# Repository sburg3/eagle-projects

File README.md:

# eagle-projects
Various projects using CadSoft Eagle.

Including:
* Seven-segment clock with atmega328 microcontroller.
* Analog ammeter clock
* Audio jack to ADC adapter for Digilent Nexys 4 DDR FPGA.

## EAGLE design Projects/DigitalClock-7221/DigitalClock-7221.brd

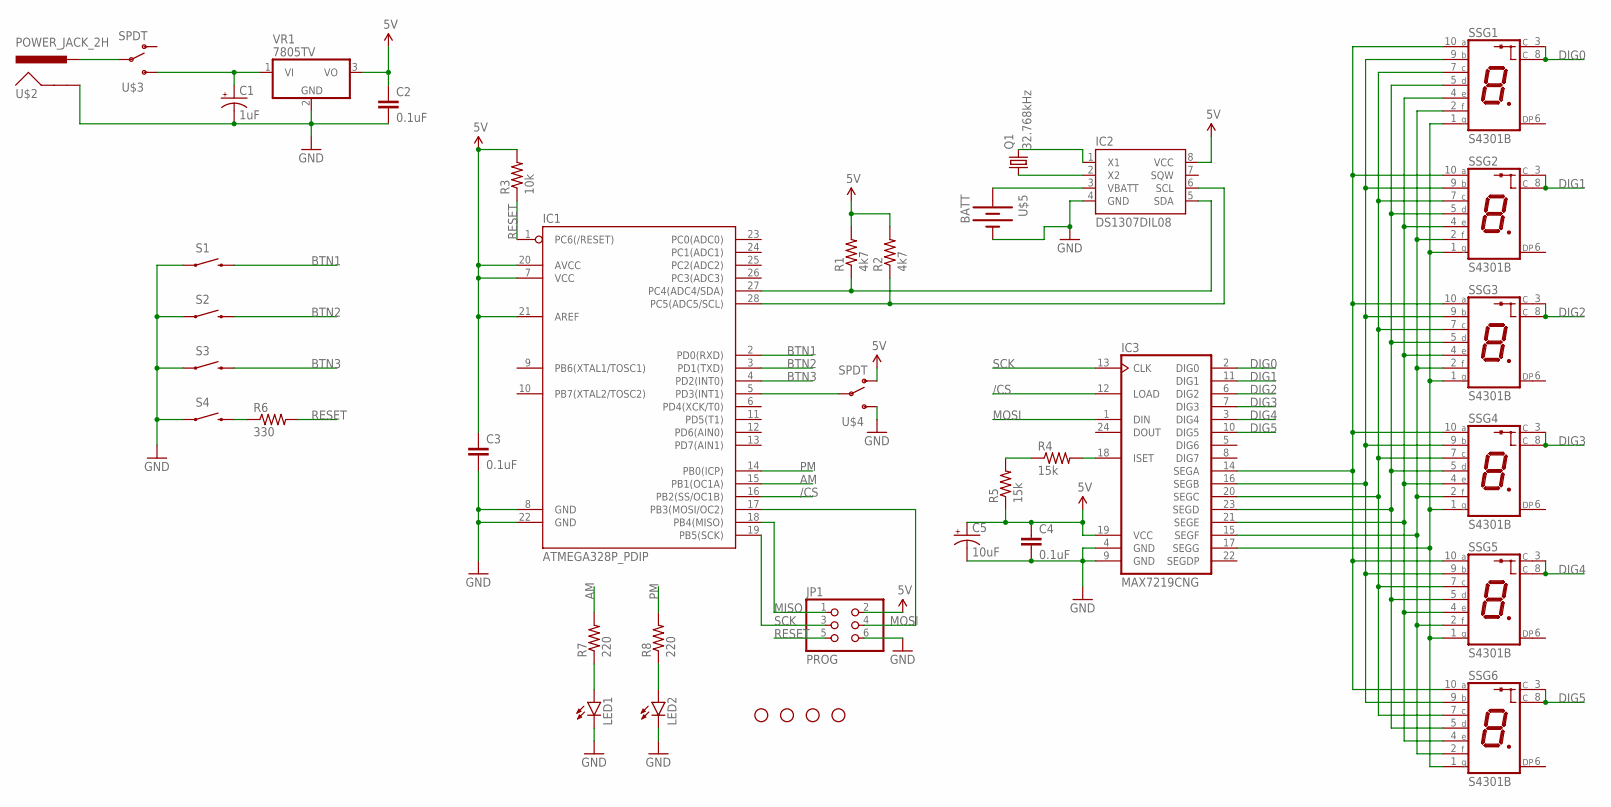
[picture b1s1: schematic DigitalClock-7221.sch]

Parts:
C1: 1uF; CPOL-RADIAL-10UF-25V
C2, C3, C4: 0.1uF; CAP-PTH-5MM
C5: 10uF; CPOL-RADIAL-10UF-25V
H1, H2, H3, H4: STAND-OFF
IC1: ATMEGA328P_PDIP; DIL28-3
IC2: DS1307DIL08; DIL08
IC3: MAX7219CNG; DIL24-3
JP1: PROG; 2X03
LED1, LED2: LED5MM
Q1: 32.768kHz; TC26V
R1, R2: 4k7; AXIAL-0.3
R3: 10k; AXIAL-0.3
R4, R5: 15k; AXIAL-0.3
R6: 330; AXIAL-0.3
R7, R8: 220; AXIAL-0.3
S1, S2, S3, S4: SWITCH-MOMENTARY-2PTH; TACTILE-PTH
SSG1, SSG2, SSG3, SSG4, SSG5, SSG6: S4301B
U$2: POWER_JACK_2H
U$3, U$4: SPDT
U$5: BATT
VR1: 7805TV; TO220V

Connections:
5V: C2.1, C3.1, C4.1, C5.1 (+), IC1.7 (VCC), IC1.20 (AVCC), IC1.21 (AREF), IC2.8 (VCC), IC3.19 (VCC), JP1.2, R1.P$2 (2), R2.P$2 (2), R3.P$2 (2), R5.P$1 (1), U$4.P$2 (O), VR1.3 (VO)
/CS: IC1.16 (PB2(SS/OC1B)), IC3.12 (LOAD)
AM: IC1.15 (PB1(OC1A)), R7.P$2 (2)
BTN1: IC1.2 (PD0(RXD)), S1.3 (2)
BTN2: IC1.3 (PD1(TXD)), S2.3 (2)
BTN3: IC1.4 (PD2(INT0)), S3.3 (2)
DIG0: IC3.2 (DIG0), SSG1.3 (C), SSG1.8 (C)
DIG1: IC3.11 (DIG1), SSG2.3 (C), SSG2.8 (C)
DIG2: IC3.6 (DIG2), SSG3.3 (C), SSG3.8 (C)
DIG3: IC3.7 (DIG3), SSG4.3 (C), SSG4.8 (C)
DIG4: IC3.3 (DIG4), SSG5.3 (C), SSG5.8 (C)
DIG5: IC3.10 (DIG5), SSG6.3 (C), SSG6.8 (C)
GND: C1.2 (-), C2.2, C3.2, C4.2, C5.2 (-), IC1.8 (GND), IC1.22 (GND), IC2.4 (GND), IC3.4 (GND), IC3.9 (GND), JP1.6, LED1.K (C), LED2.K (C), S1.1, S2.1, S3.1, S4.1, U$2.P$1 (GND), U$4.P$3 (S), U$5.P$2 (-), VR1.2 (GND)
MISO: IC1.18 (PB4(MISO)), JP1.1
MOSI: IC1.17 (PB3(MOSI/OC2)), IC3.1 (DIN), JP1.4
unnamed: U$2.P$2 (PWR), U$3.P$1
unnamed: C1.1 (+), U$3.P$3 (S), VR1.1 (VI)
unnamed: IC2.2 (X2), Q1.1
unnamed: IC2.1 (X1), Q1.2
unnamed: IC1.5 (PD3(INT1)), U$4.P$1
unnamed: R6.P$1 (1), S4.3 (2)
unnamed: LED2.A, R8.P$1 (1)
unnamed: LED1.A, R7.P$1 (1)
unnamed: IC3.18 (ISET), R4.P$2 (2)
unnamed: IC2.3 (VBATT), U$5.P$1 (+)
unnamed: IC1.27 (PC4(ADC4/SDA)), IC2.5 (SDA), R1.P$1 (1)
unnamed: IC1.28 (PC5(ADC5/SCL)), IC2.6 (SCL), R2.P$1 (1)
unnamed: R4.P$1 (1), R5.P$2 (2)
unnamed: IC3.17 (SEGG), SSG1.1 (G), SSG2.1 (G), SSG3.1 (G), SSG4.1 (G), SSG5.1 (G), SSG6.1 (G)
unnamed: IC3.15 (SEGF), SSG1.2 (F), SSG2.2 (F), SSG3.2 (F), SSG4.2 (F), SSG5.2 (F), SSG6.2 (F)
unnamed: IC3.21 (SEGE), SSG1.4 (E), SSG2.4 (E), SSG3.4 (E), SSG4.4 (E), SSG5.4 (E), SSG6.4 (E)
unnamed: IC3.23 (SEGD), SSG1.5 (D), SSG2.5 (D), SSG3.5 (D), SSG4.5 (D), SSG5.5 (D), SSG6.5 (D)
unnamed: IC3.20 (SEGC), SSG1.7 (C), SSG2.7 (C), SSG3.7 (C), SSG4.7 (C), SSG5.7 (C), SSG6.7 (C)
unnamed: IC3.16 (SEGB), SSG1.9 (B), SSG2.9 (B), SSG3.9 (B), SSG4.9 (B), SSG5.9 (B), SSG6.9 (B)
unnamed: IC3.14 (SEGA), SSG1.10 (A), SSG2.10 (A), SSG3.10 (A), SSG4.10 (A), SSG5.10 (A), SSG6.10 (A)
PM: IC1.14 (PB0(ICP)), R8.P$2 (2)
RESET: IC1.1 (PC6(/RESET)), JP1.5, R3.P$1 (1), R6.P$2 (2)
SCK: IC1.19 (PB5(SCK)), IC3.13 (CLK), JP1.3

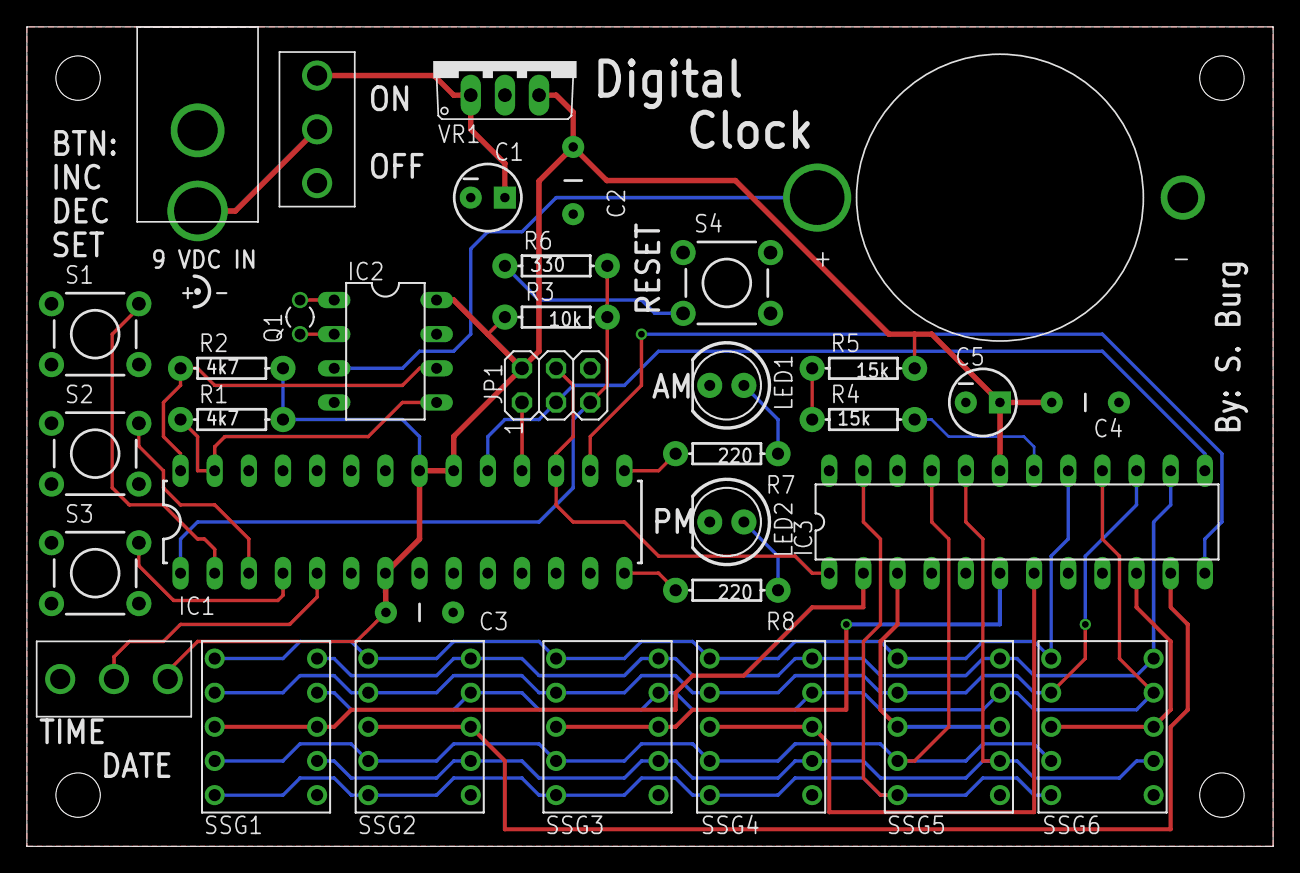
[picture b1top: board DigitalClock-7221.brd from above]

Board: 2 copper layers, 92.7 x 61.0 mm, 39 parts (0 on the bottom side), 38 nets.

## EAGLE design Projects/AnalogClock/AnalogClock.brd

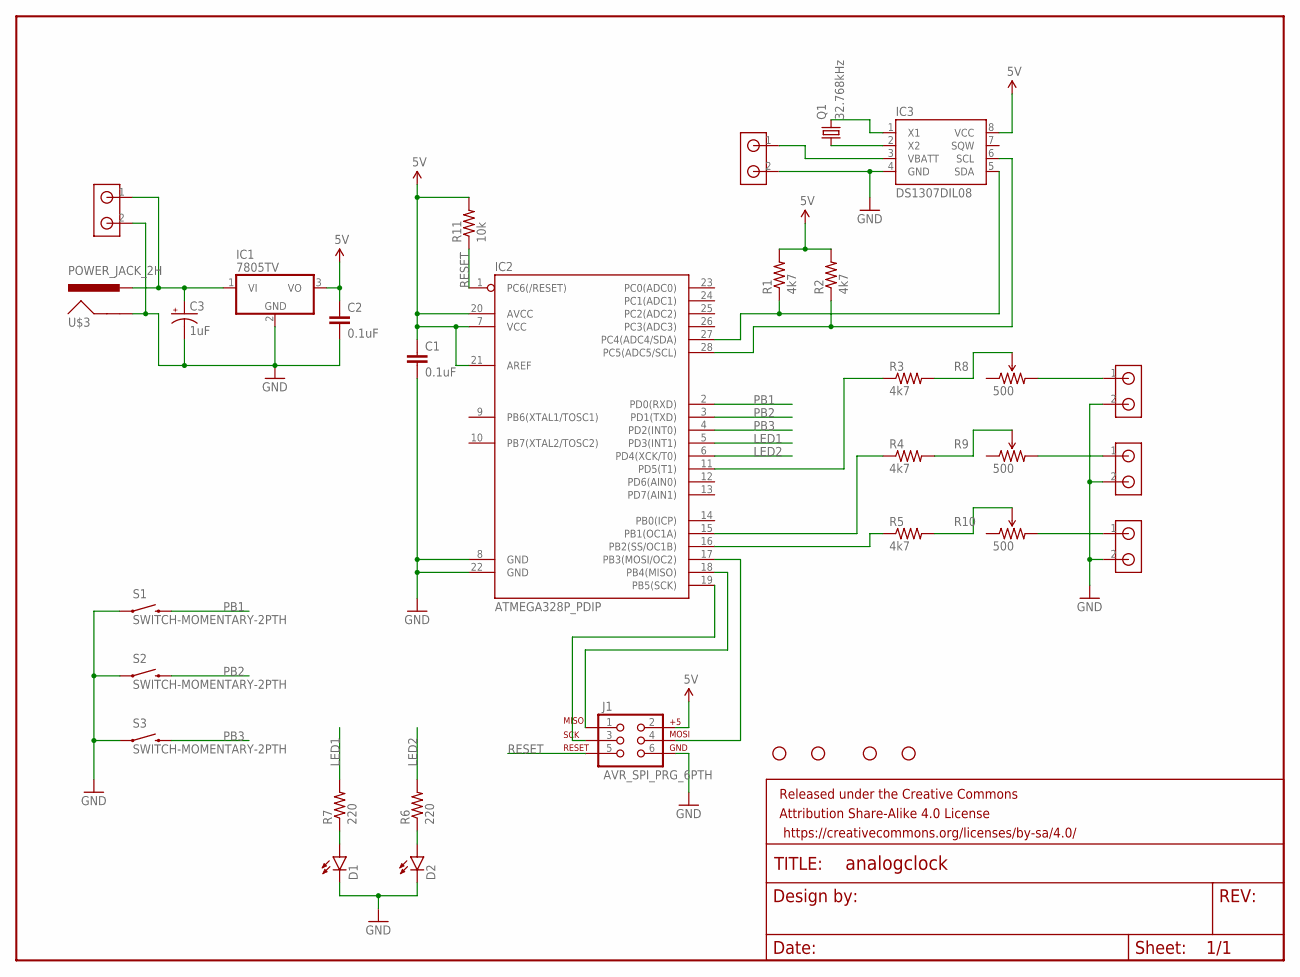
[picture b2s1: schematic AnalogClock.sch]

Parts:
C1, C2: 0.1uF; CAP-PTH-SMALL
C3: 1uF; CPOL-RADIAL-10UF-25V
D1, D2: LED3MM
FRAME1: FRAME-LETTERNO_PACKAGE; DUMMY
H1, H2, H3, H4: STAND-OFF
IC1: 7805TV; TO220V
IC2: ATMEGA328P_PDIP; DIL28-3
IC3: DS1307DIL08; DIL08
J1: AVR_SPI_PRG_6PTH; 2X3
Q1: 32.768kHz; TC26V
R1, R2, R3, R4, R5: 4k7; AXIAL-0.4
R6, R7: 220; AXIAL-0.4
R8, R9, R10: 500; TRIMPOT
R11: 10k; AXIAL-0.4
S1, S2, S3: SWITCH-MOMENTARY-2PTH; TACTILE-PTH
U$1, U$4, U$5, U$6, U$7: TBLOCK
U$3: POWER_JACK_2H

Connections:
5V: C1.1, C2.1, IC1.3 (VO), IC2.7 (VCC), IC2.20 (AVCC), IC2.21 (AREF), IC3.8 (VCC), J1.2, R1.P$2 (2), R2.P$2 (2), R11.P$2 (2)
GND: C1.2, C2.2, C3.2 (-), D1.K (C), D2.K (C), IC1.2 (GND), IC2.8 (GND), IC2.22 (GND), IC3.4 (GND), J1.6, S1.1, S2.1, S3.1, U$1.2, U$3.P$1 (GND), U$4.2, U$5.2, U$6.2, U$7.2
LED1: IC2.5 (PD3(INT1)), R7.P$2 (2)
LED2: IC2.6 (PD4(XCK/T0)), R6.P$2 (2)
unnamed: R3.P$2 (2), R8.P$3 (WIPER)
unnamed: R4.P$2 (2), R9.P$3 (WIPER)
unnamed: R5.P$2 (2), R10.P$3 (WIPER)
unnamed: R8.P$2 (CW), U$4.1
unnamed: R9.P$2 (CW), U$6.1
unnamed: R10.P$2 (CW), U$7.1
unnamed: C3.1 (+), IC1.1 (VI), U$3.P$2 (PWR), U$5.1
unnamed: IC2.19 (PB5(SCK)), J1.3
unnamed: IC2.27 (PC4(ADC4/SDA)), IC3.5 (SDA), R1.P$1 (1)
unnamed: IC2.28 (PC5(ADC5/SCL)), IC3.6 (SCL), R2.P$1 (1)
unnamed: IC2.11 (PD5(T1)), R3.P$1 (1)
unnamed: IC2.17 (PB3(MOSI/OC2)), J1.4
unnamed: IC2.18 (PB4(MISO)), J1.1
unnamed: IC3.1 (X1), Q1.2
unnamed: IC3.2 (X2), Q1.1
unnamed: IC3.3 (VBATT), U$1.1
unnamed: IC2.15 (PB1(OC1A)), R4.P$1 (1)
unnamed: IC2.16 (PB2(SS/OC1B)), R5.P$1 (1)
unnamed: D1.A, R7.P$1 (1)
unnamed: D2.A, R6.P$1 (1)
PB1: IC2.2 (PD0(RXD)), S1.3 (2)
PB2: IC2.3 (PD1(TXD)), S2.3 (2)
PB3: IC2.4 (PD2(INT0)), S3.3 (2)
RESET: IC2.1 (PC6(/RESET)), J1.5, R11.P$1 (1)

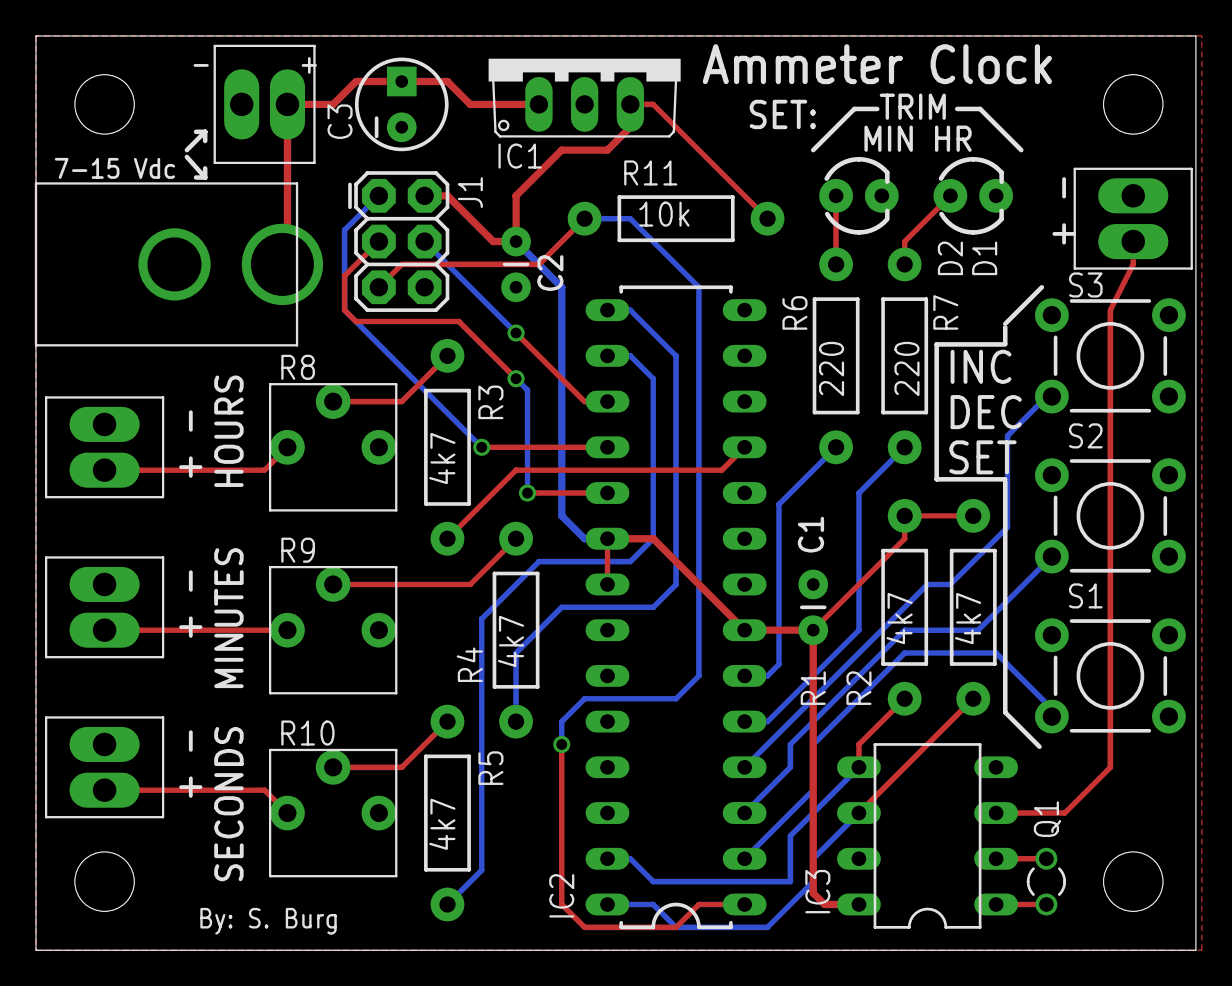
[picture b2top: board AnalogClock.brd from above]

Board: 2 copper layers, 64.4 x 50.8 mm, 35 parts (0 on the bottom side), 28 nets.

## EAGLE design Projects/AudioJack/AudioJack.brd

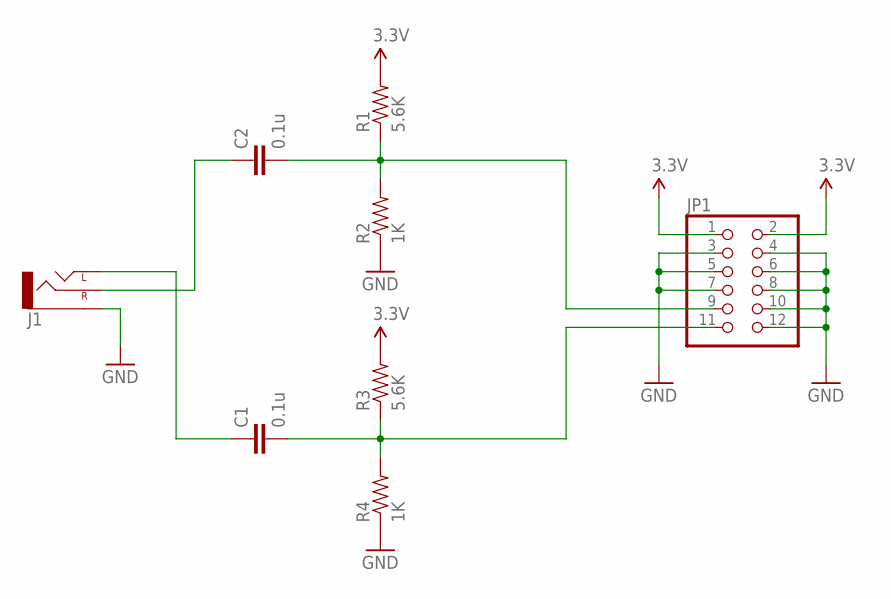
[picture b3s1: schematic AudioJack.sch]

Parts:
C1, C2: 0.1u; CAP-PTH-5MM
J1: AUDIO-JACKPTH; AUDIO-JACK
JP1: PINHD-2X6/90; 2X06/90
R1, R3: 5.6K; AXIAL-0.4
R2, R4: 1K; AXIAL-0.4

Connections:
3.3V: JP1.1, JP1.2, R1.P$2 (2), R3.P$2 (2)
GND: J1.SLEEVE, JP1.3, JP1.4, JP1.5, JP1.6, JP1.7, JP1.8, JP1.10, JP1.12, R2.P$1 (1), R4.P$1 (1)
unnamed: C2.1, J1.RING (RIGHT)
unnamed: C1.1, J1.TIP (LEFT)
unnamed: C2.2, JP1.9, R1.P$1 (1), R2.P$2 (2)
unnamed: C1.2, JP1.11, R3.P$1 (1), R4.P$2 (2)

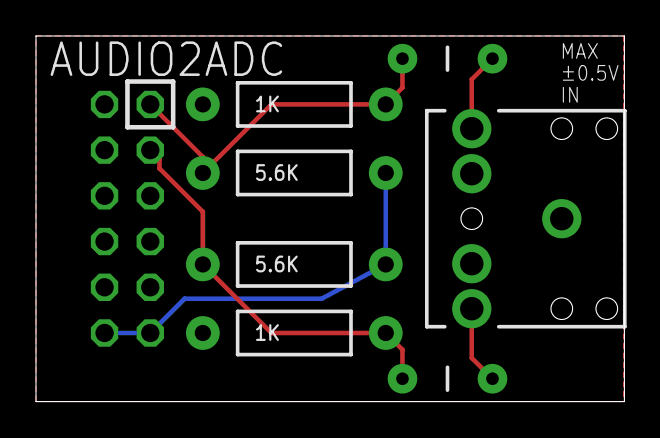
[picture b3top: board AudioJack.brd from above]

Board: 2 copper layers, 32.7 x 20.3 mm, 8 parts (0 on the bottom side), 6 nets.

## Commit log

2016-06-01 Change readme

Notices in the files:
parts and their libraries:
SparkFun-Capacitors: Licensing: Creative Commons ShareAlike 4.0 International - https://creativecommons.org/licenses/by-sa/4.0
SparkFun-Aesthetics: Released under the Creative Commons Attribution Share-Alike 4.0 License
SparkFun-Aesthetics: https://creativecommons.org/licenses/by-sa/4.0
